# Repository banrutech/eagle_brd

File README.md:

# eagle_brd
there are eagle .brd and .sch I make in this repo
each file must separate each branch

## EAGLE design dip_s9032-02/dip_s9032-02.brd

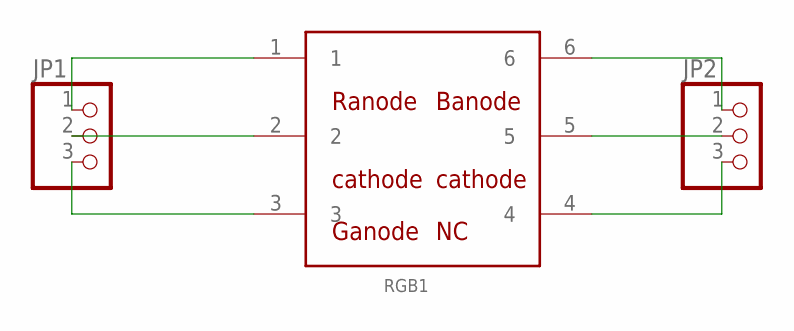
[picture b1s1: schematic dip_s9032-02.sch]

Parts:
JP1, JP2: PINHD-1X3; 1X03
RGB1: S9032-02; RGB_SENSOR

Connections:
unnamed: JP1.1, RGB1.1
unnamed: JP1.2, RGB1.2
unnamed: JP1.3, RGB1.3
unnamed: JP2.1, RGB1.6
unnamed: JP2.2, RGB1.5
unnamed: JP2.3, RGB1.4

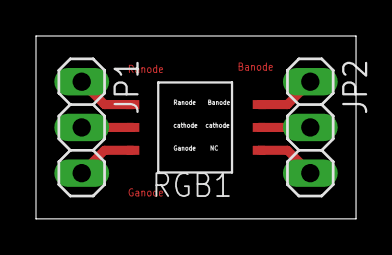
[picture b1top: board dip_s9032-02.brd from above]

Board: 2 copper layers, 17.8 x 10.2 mm, 3 parts (0 on the bottom side), 6 nets.

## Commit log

2018-11-22 make dip_s9032-02
2018-12-16 finish
